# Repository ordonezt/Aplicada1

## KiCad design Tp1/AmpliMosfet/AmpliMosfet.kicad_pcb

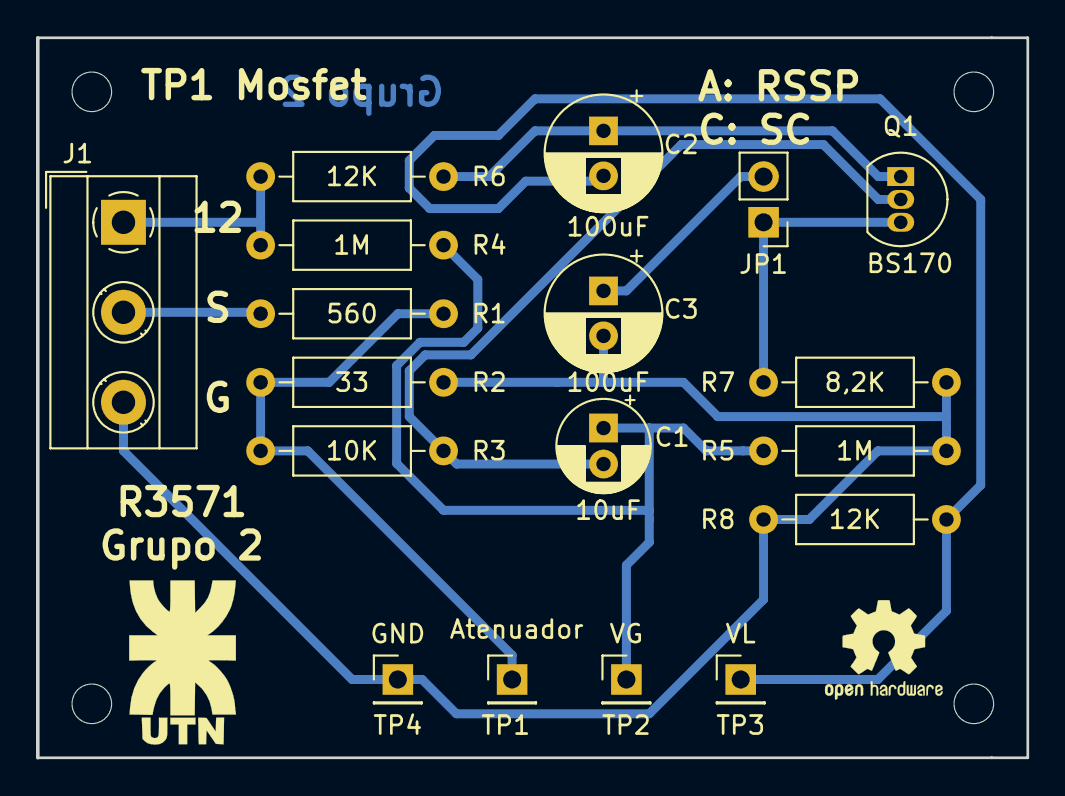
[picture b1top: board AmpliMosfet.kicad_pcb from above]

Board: 2 copper layers, 55.0 x 40.0 mm, 18 parts (0 on the bottom side), 10 nets.

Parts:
C1: 10uF; CP_Radial_D5.0mm_P2.00mm
C2, C3: 100uF; CP_Radial_D6.3mm_P2.50mm
J1: Screw_Terminal_01x03; TerminalBlock_MetzConnect_Type055_RT01503HDWU_1x03_P5.00mm_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
JP1: Jumper; PinHeader_1x02_P2.54mm_Vertical
Q1: BS170; TO-92_Inline
R1: 560; R_Axial_DIN0207_L6.3mm_D2.5mm_P10.16mm_Horizontal
R2: 33; R_Axial_DIN0207_L6.3mm_D2.5mm_P10.16mm_Horizontal
R3: 10K; R_Axial_DIN0207_L6.3mm_D2.5mm_P10.16mm_Horizontal
R4, R5: 1M; R_Axial_DIN0207_L6.3mm_D2.5mm_P10.16mm_Horizontal
R6, R8: 12K; R_Axial_DIN0207_L6.3mm_D2.5mm_P10.16mm_Horizontal
R7: 8,2K; R_Axial_DIN0207_L6.3mm_D2.5mm_P10.16mm_Horizontal
TP1, TP2, TP3, TP4: TestPoint; PinHeader_1x01_P2.54mm_Vertical

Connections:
+12V: J1.1, R4.1, R6.1
AC: J1.2, R1.2
GND: C3.2, J1.3, R2.2, R5.2, R7.2, R8.2, TP4.1
unnamed: C1.1, R4.2, R5.1, TP2.1
unnamed: C1.2, Q1.2, R3.1
unnamed: C2.1, Q1.1, R6.2
unnamed: C2.2, R8.1, TP3.1
unnamed: C3.1, JP1.2
unnamed: JP1.1, Q1.3, R7.1
unnamed: R1.1, R2.1, R3.2, TP1.1

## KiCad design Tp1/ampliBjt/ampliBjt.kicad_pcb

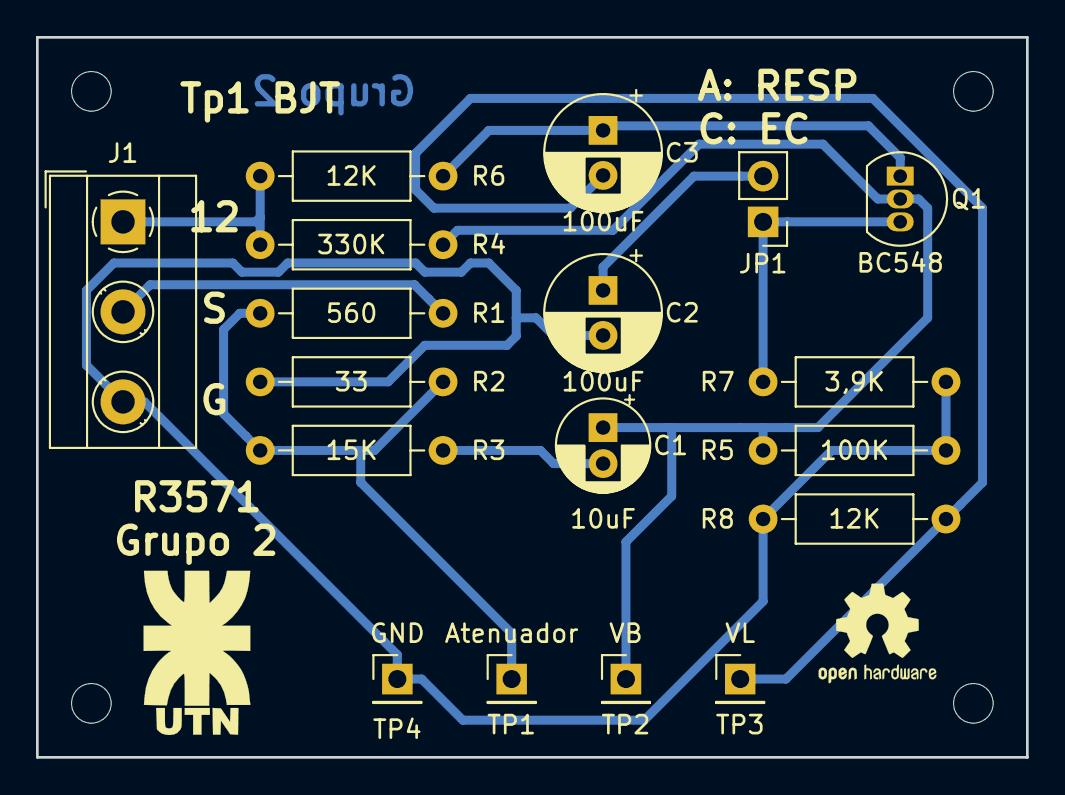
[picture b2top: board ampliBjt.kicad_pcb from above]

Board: 2 copper layers, 55.0 x 40.0 mm, 18 parts (0 on the bottom side), 10 nets.

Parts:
C1: 10uF; CP_Radial_D5.0mm_P2.00mm
C2, C3: 100uF; CP_Radial_D6.3mm_P2.50mm
J1: Screw_Terminal_01x03; TerminalBlock_MetzConnect_Type055_RT01503HDWU_1x03_P5.00mm_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
JP1: Jumper; PinHeader_1x02_P2.54mm_Vertical
Q1: BC548; TO-92_Inline
R1: 560; R_Axial_DIN0207_L6.3mm_D2.5mm_P10.16mm_Horizontal
R2: 33; R_Axial_DIN0207_L6.3mm_D2.5mm_P10.16mm_Horizontal
R3: 15K; R_Axial_DIN0207_L6.3mm_D2.5mm_P10.16mm_Horizontal
R4: 330K; R_Axial_DIN0207_L6.3mm_D2.5mm_P10.16mm_Horizontal
R5: 100K; R_Axial_DIN0207_L6.3mm_D2.5mm_P10.16mm_Horizontal
R6, R8: 12K; R_Axial_DIN0207_L6.3mm_D2.5mm_P10.16mm_Horizontal
R7: 3,9K; R_Axial_DIN0207_L6.3mm_D2.5mm_P10.16mm_Horizontal
TP1: Atenuador; PinHeader_1x01_P2.54mm_Vertical
TP2: VB; PinHeader_1x01_P2.54mm_Vertical
TP3: VL; PinHeader_1x01_P2.54mm_Vertical
TP4: GND; PinHeader_1x01_P2.54mm_Vertical

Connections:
AC: J1.2, R1.1
Earth: C2.2, J1.3, R2.1, R5.2, R7.2, R8.1, TP4.1
unnamed: C1.1, Q1.2, R4.2, R5.1, TP2.1
unnamed: C1.2, R3.1
unnamed: C2.1, JP1.2
unnamed: C3.1, Q1.1, R6.2
unnamed: C3.2, R8.2, TP3.1
unnamed: JP1.1, Q1.3, R7.1
unnamed: R1.2, R2.2, R3.2, TP1.1
VCC: J1.1, R4.1, R6.1

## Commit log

2018-09-26 Agrego ambas partes del tp1
2018-09-26 Mosfet terminado, BJT faltan las resistencias
2018-09-26 BJT terminado
